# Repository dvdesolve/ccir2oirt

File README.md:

# ccir2oirt
This converter is intended for shifting radio frequency down so old radio receivers which works in OIRT range (mostly produced in Soviet Union) become able to receive modern CCIR range. It have 3 frequency range selectors: 88-96, 95-103 and 101-109 MHz. Input voltage is quite wide and spans from 7V to 25V (for both positive and negative versions). It's recommended to place the whole device in solid aluminum box to prevent unintended RF interference.

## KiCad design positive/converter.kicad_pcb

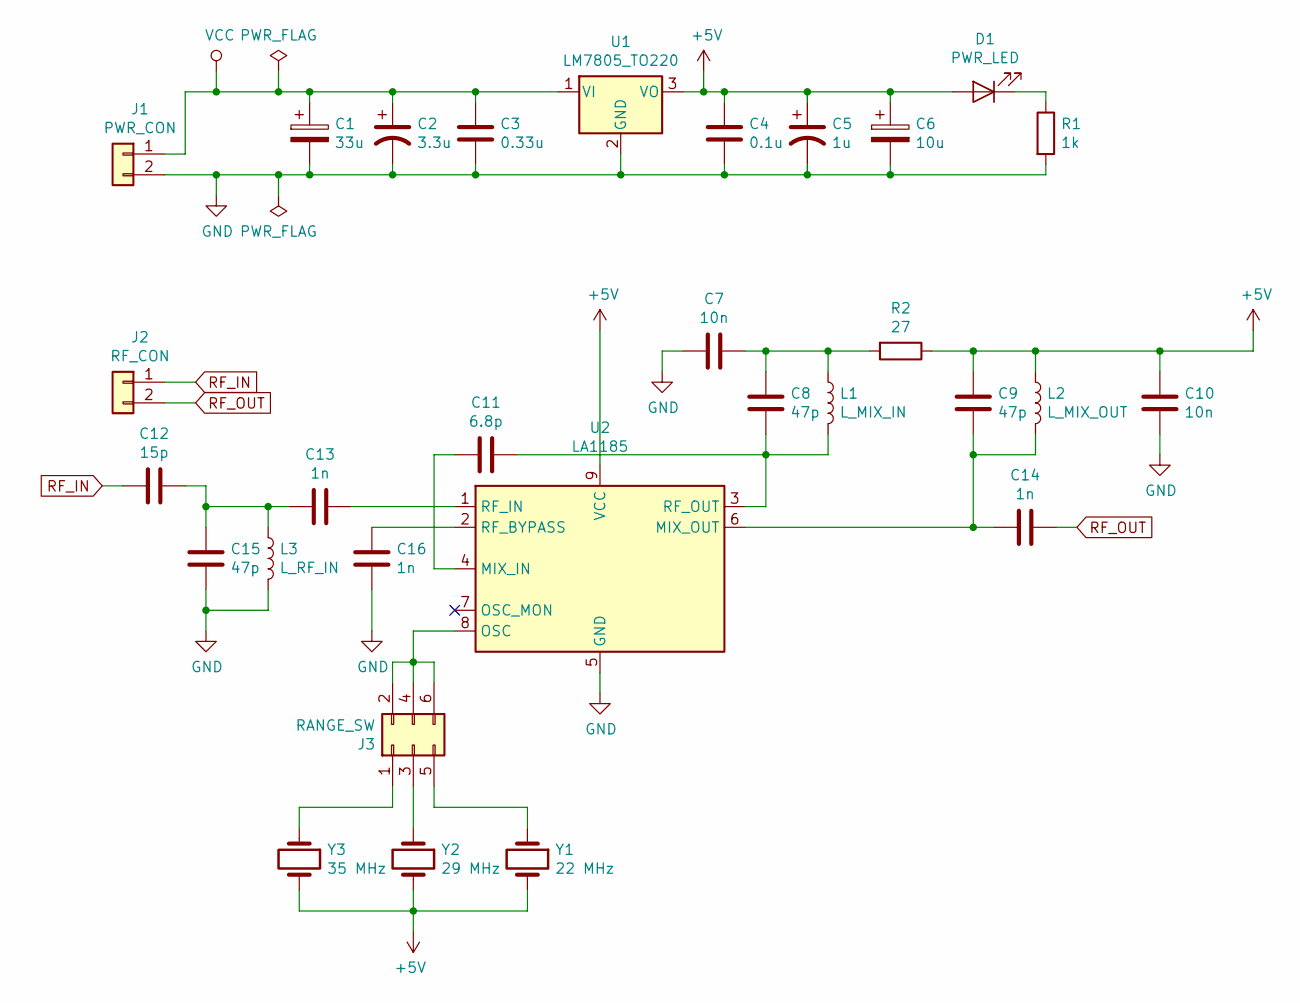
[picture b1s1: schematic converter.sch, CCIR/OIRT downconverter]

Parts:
C1: 33u; CP_Radial_D5.0mm_P2.00mm
C2: 3.3u; CP_EIA-3528-21_Kemet-B_Pad1.50x2.35mm_HandSolder
C3: 0.33u; C_Disc_D4.7mm_W2.5mm_P5.00mm
C4: 0.1u; C_Disc_D4.7mm_W2.5mm_P5.00mm
C5: 1u; CP_EIA-3216-18_Kemet-A_Pad1.58x1.35mm_HandSolder
C6: 10u; CP_Radial_D5.0mm_P2.00mm
C7, C10: 10n; C_Disc_D4.7mm_W2.5mm_P5.00mm
C8, C9, C15: 47p; C_Disc_D4.7mm_W2.5mm_P5.00mm
C11: 6.8p; C_Rect_L6.8mm_W4.6mm_P2.50mm
C12: 15p; C_Disc_D4.7mm_W2.5mm_P5.00mm
C13, C14, C16: 1n; C_Disc_D4.7mm_W2.5mm_P5.00mm
D1: PWR_LED; LED_D5.0mm
J1: PWR_CON; Connfly_DS1070-2MR_1x02_P2.54mm
J2: RF_CON; Connfly_DS1070-2MR_1x02_P2.54mm
J3: RANGE_SW; PinHeader_2x03_P2.54mm_Horizontal
L1: L_MIX_IN; L_Axial_4Turns_d0.8mm_D4.5mm_WP1.0mm
L2: L_MIX_OUT; L_Axial_6Turns_d0.8mm_D4.5mm_WP1.0mm
L3: L_RF_IN; L_Axial_4Turns_d0.8mm_D4.5mm_WP1.0mm
R1: 1k; R_Axial_DIN0207_L6.3mm_D2.5mm_P10.16mm_Horizontal
R2: 27; R_Axial_DIN0207_L6.3mm_D2.5mm_P10.16mm_Horizontal
U1: LM7805_TO220; TO-220-3_Vertical
U2: LA1185; SIP-9_21.54x3mm_P2.54mm
Y1: 22 MHz; Crystal_HC49-U_Vertical
Y2: 29 MHz; Crystal_HC49-U_Vertical
Y3: 35 MHz; Crystal_HC49-U_Vertical

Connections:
+5V: C4.1, C5.1, C6.1, C9.1, C10.1, D1.2 (A), L2.1, R2.1, U1.3 (VO), U2.9 (VCC), Y1.2, Y2.2, Y3.2
GND: C1.2, C2.2, C3.2, C4.2, C5.2, C6.2, C7.2, C10.2, C15.2, C16.2, J1.2, L3.2, R1.2, U1.2 (GND), U2.5 (GND); also elsewhere on the board
unnamed: C7.1, C8.1, L1.1, R2.2
unnamed: C8.2, C11.1, L1.2, U2.3 (RF_OUT)
unnamed: C11.2, U2.4 (MIX_IN)
unnamed: C12.1, C13.2, C15.1, L3.1
unnamed: C13.1, U2.1 (RF_IN)
unnamed: C9.2, C14.2, L2.2, U2.6 (MIX_OUT)
unnamed: C16.1, U2.2 (RF_BYPASS)
unnamed: D1.1 (K), R1.1
unnamed: J3.1, Y3.1
unnamed: J3.2, J3.4, J3.6, U2.8 (OSC)
unnamed: J3.3, Y2.1
unnamed: J3.5, Y1.1
RF_IN: C12.2, J2.1
RF_OUT: C14.1, J2.2
VCC: C1.1, C2.1, C3.1, J1.1, U1.1 (VI)

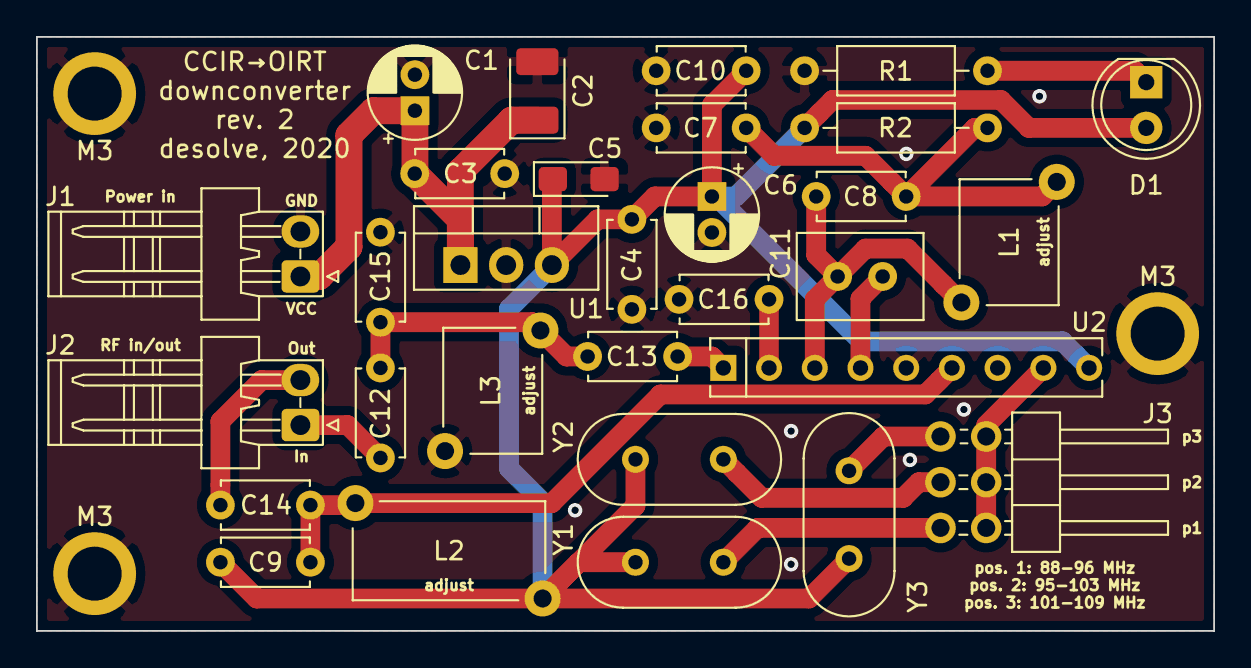
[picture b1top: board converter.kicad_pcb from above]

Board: 2 copper layers, 65.4 x 33.0 mm, 33 parts (0 on the bottom side), 17 nets.

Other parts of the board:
M3, M3#2, M3#3: M3; Pin_D1.0mm_L10.0mm

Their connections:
GND: M3.1, M3#2.1, M3#3.1; also elsewhere on the board

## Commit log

2020-03-08 Add project files
